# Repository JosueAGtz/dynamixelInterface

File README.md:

# Dynamixel Interface
The Dynamixel Interface is a board that allows easy communication with an MCU or Processor with a simple UART module, the board integrates a voltage level converter and a Tri-state buffer to accomplish good communication between a Dynamixel servomotor and almost any microcontroller in the market. The board is breadboard-friendly and development-ready as the connection pins are 0.1" standard pitch and the castellated holes for SMD mounting.

Get the assembled interface on my Tindie Store:  https://www.tindie.com/products/17747/

## Dynamixel Interface Wiring 

## Dynamixel Interface Features and Pinout

## Dynamixel Interface Dimensions

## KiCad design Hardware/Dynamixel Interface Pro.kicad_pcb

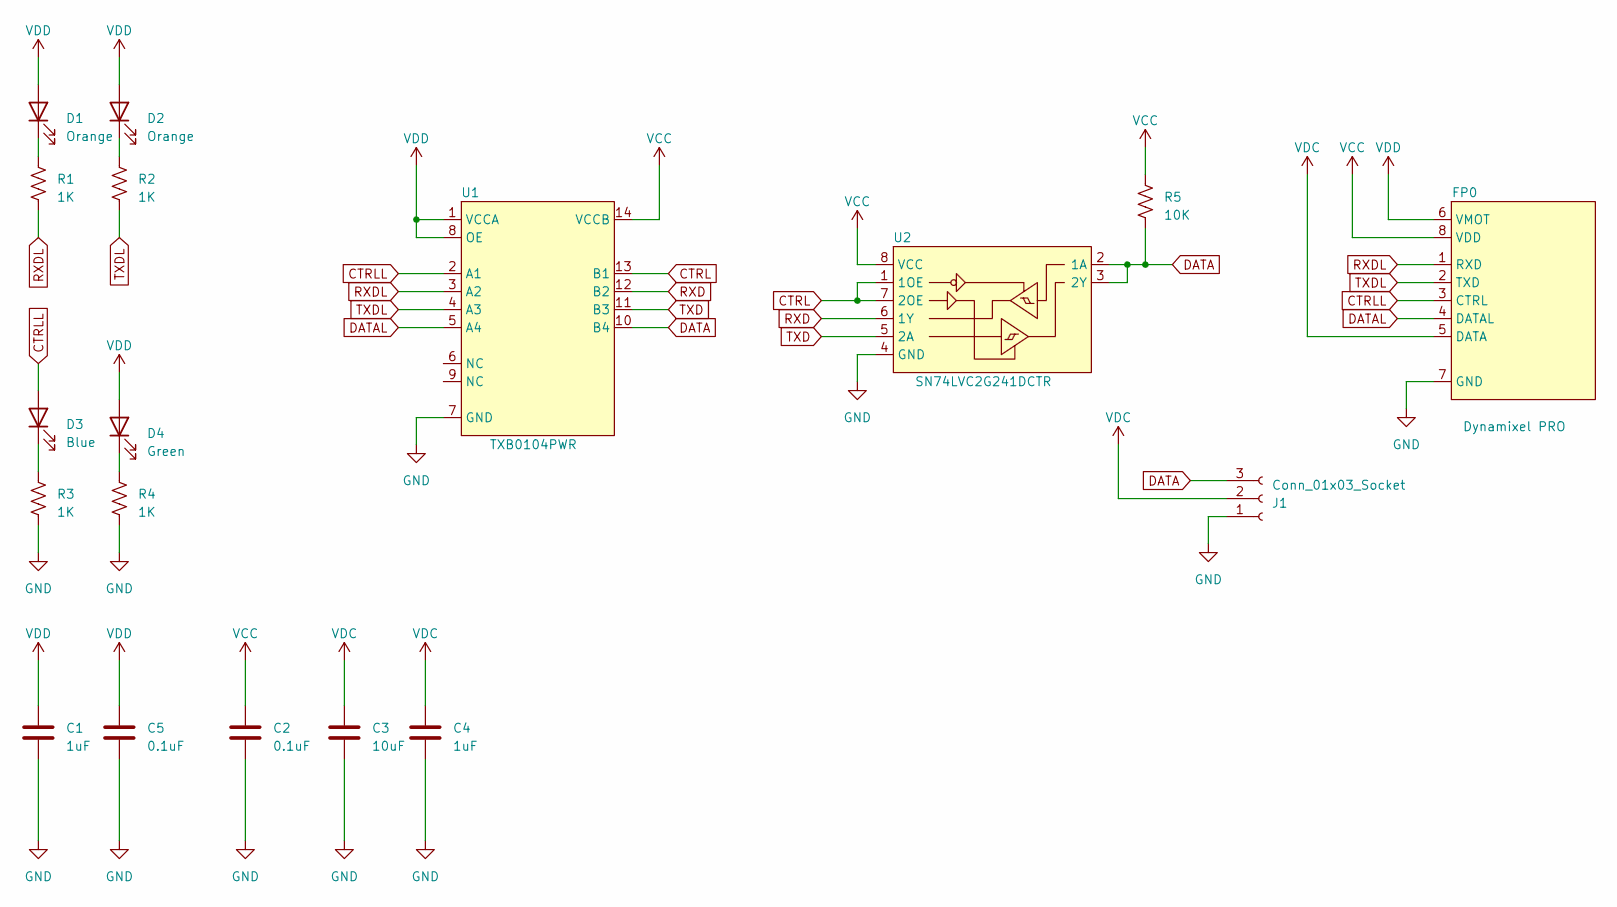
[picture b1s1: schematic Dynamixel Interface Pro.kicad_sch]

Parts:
C1: 1uF; C_0402_1005Metric
C2, C5: 0.1uF; C_0402_1005Metric
C3: 10uF; C_0603_1608Metric
C4: 1uF; C_0603_1608Metric
D1, D2: Orange; 0402LED
D3: Blue; 0402LED
D4: Green; 0402LED
FP0: Dynamixel PRO; Dynamixel_Driver
J1: Conn_01x03_Socket; JST_EH_S3B-EH_1x03_P2.50mm_Horizontal
R1, R2, R3, R4: 1K; R_0402_1005Metric
R5: 10K; R_0402_1005Metric
U1: TXB0104PWR; TSSOP14_5x4.4_0.65
U2: SN74LVC2G241DCTR; VSSOP-8_2.3x2mm_P0.5mm

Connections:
CTRL: U1.13 (B1), U2.1 (1OE), U2.7 (2OE)
CTRLL: D3.2 (A), FP0.3 (CTRL), U1.2 (A1)
DATA: J1.3, R5.2, U1.10 (B4), U2.2 (1A), U2.3 (2Y)
DATAL: FP0.4 (DATAL), U1.5 (A4)
GND: C1.2, C2.2, C3.2, C4.2, C5.2, FP0.7 (GND), J1.1, R3.2, R4.2, U1.7 (GND), U2.4 (GND)
unnamed: D1.1 (K), R1.1
unnamed: D2.1 (K), R2.1
unnamed: D3.1 (K), R3.1
unnamed: D4.1 (K), R4.1
RXD: U1.12 (B2), U2.6 (1Y)
RXDL: FP0.1 (RXD), R1.2, U1.3 (A2)
TXD: U1.11 (B3), U2.5 (2A)
TXDL: FP0.2 (TXD), R2.2, U1.4 (A3)
VCC: C2.1, FP0.8 (VDD), R5.1, U1.14 (VCCB), U2.8 (VCC)
VDC: C3.1, C4.1, FP0.5 (DATA), J1.2
VDD: C1.1, C5.1, D1.2 (A), D2.2 (A), D4.2 (A), FP0.6 (VMOT), U1.1 (VCCA), U1.8 (OE)

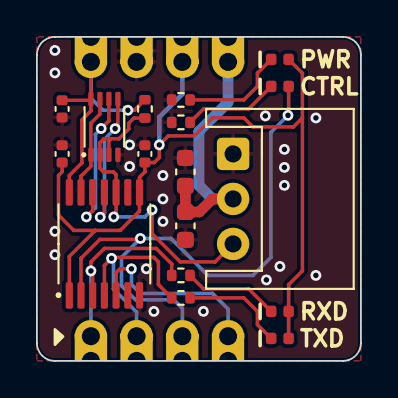
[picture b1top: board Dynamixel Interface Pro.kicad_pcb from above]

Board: 2 copper layers, 18.0 x 18.0 mm, 19 parts (1 on the bottom side), 16 nets.

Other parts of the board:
G_logoSmall: LOGO; G_SELOGO_SMALL

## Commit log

2023-10-13 Library Update and examples
2025-01-15 BOM update
